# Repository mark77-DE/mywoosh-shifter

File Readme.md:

# MyWoosh Shifter

Kleine Bluetooth-Tastatur (BLE-HID) auf Basis eines ESP32-C3 Super Mini mit vier Tastern zum Schalten und Abbiegen in MyWoosh. Die Tastenbelegung lässt sich per Handy über eine kleine Konfigurationsseite ändern.

| Taster | Pin   | Standardtaste | Funktion         |
|--------|-------|---------------|------------------|
| 1      | GPIO4 | `i`           | hochschalten     |
| 2      | GPIO5 | `k`           | herunterschalten |
| 3      | GPIO6 | Pfeil links   | links abbiegen   |
| 4      | GPIO10 | Pfeil rechts | rechts abbiegen  |

## Hardware

- ESP32-C3 Super Mini (Bluetooth 5 LE)
- 4 Taster
- 1 LED mit Vorwiderstand (ca. 1 kΩ)

## Verdrahtung

Jeder Taster wird zwischen seinen GPIO-Pin und GND geschaltet. Externe Widerstände sind nicht nötig, der interne Pull-up wird verwendet.

```
GPIO4 ──[Taster 1]── GND
GPIO5 ──[Taster 2]── GND
GPIO6 ──[Taster 3]── GND
GPIO10 ──[Taster 4]── GND
```

## Build & Upload

Voraussetzung: [PlatformIO](https://platformio.org/) (VS Code Extension oder CLI).

```bash
pio run -t upload     # build and flash
pio device monitor    # serial output (115200 baud)
```

Falls der Upload nicht startet: BOOT gedrückt halten, dabei Reset drücken und erneut flashen.

## Koppeln

1. Auf dem Gerät mit MyWoosh (PC, Tablet, Handy, Apple TV) die Bluetooth-Einstellungen öffnen.
2. Nach **"MyWoosh Shifter"** suchen und koppeln.
3. In MyWoosh schalten die Taster nun hoch, runter und biegen links bzw. rechts ab (Standardbelegung).

## Status-LED

Eine LED an GPIO9 zeigt den Zustand an:

| LED                     | Bedeutung                              |
|-------------------------|----------------------------------------|
| blinkt langsam          | nicht verbunden, wartet auf Kopplung   |
| 3 Sekunden an, dann aus | mit dem Gerät verbunden                |
| blinkt schnell          | Konfigurationsmodus, Hotspot aktiv     |
| Doppelblinken           | Konfigurationsmodus, Client verbunden  |

Verdrahtung: 3V3, Vorwiderstand, LED, GPIO9. Die LED leuchtet also, wenn der Pin LOW ist.

Wichtig: GPIO9 ist ein Strapping-Pin (BOOT-Taster). Eine LED, die nach GND führt, würde den Pin beim Start nach unten ziehen und den ESP in den Download-Modus zwingen.

## Tasten per Handy zuordnen

Funktioniert auf Android und iOS, ohne App.

1. Taster 1 gedrückt halten und gleichzeitig den ESP mit Strom versorgen (z. B. USB einstecken). Nach etwa 1,5 Sekunden startet der Hotspot, die LED blinkt schnell.
2. Mit dem Handy das offene WLAN **MyWoosh-Shifter-Setup** verbinden (kein Passwort).
3. Die Konfigurationsseite öffnet sich meist automatisch. Sonst im Browser `http://192.168.4.1` aufrufen.
4. Für jeden Taster die gewünschte Taste wählen und auf **Speichern & neu starten** tippen.
5. Der ESP startet neu, der Hotspot ist danach wieder aus und die Belegung bleibt gespeichert.

Zur Auswahl stehen Buchstaben, Ziffern, F1 bis F12, Pfeiltasten, Enter, Esc, Leertaste, Tab, Bild auf/ab, Pos1 und Ende. Mit "keine" wird ein Taster deaktiviert.

Im Konfigurationsmodus ist Bluetooth aus, im normalen Betrieb ist WLAN aus. Die bestehende Kopplung mit MyWoosh bleibt davon unberührt.

## Konfiguration im Code

Oben in `src/main.cpp` lassen sich anpassen:

- `PIN_BTN`: GPIO-Pins der vier Taster
- `PIN_LED`, `LED_ACTIVE_LOW`: LED-Pin und Polarität (`true`: LED leuchtet bei LOW)
- `BLINK_MS`, `CONFIG_BLINK_MS`, `CONNECTED_SHOW_MS`: Blinkgeschwindigkeit und Leuchtdauer nach dem Verbinden
- `AP_SSID`: Name des Konfigurations-WLANs
- `CONFIG_HOLD_MS`: wie lange Taster 1 beim Einschalten gehalten werden muss
- `DEFAULT_KEYS`: Standardbelegung, solange noch nichts gespeichert wurde

In der Liste `buttons` legt das Feld `hold` fest, ob eine Taste nur kurz angetippt wird (`false`, Standard) oder gedrückt bleibt, solange der Taster gehalten wird (`true`).

## Hinweise

- Wichtig: Platform und Bibliothek müssen zusammenpassen. In der `platformio.ini` sind `espressif32@6.9.0` und `NimBLE-Arduino@1.4.3` fest gepinnt. Mit der neueren Platform (Arduino-Core 3.x) gibt es viele Build-Warnungen und einen Boot-Loop beim Start von BLE.
- Nach einem Wechsel der Versionen den Ordner `.pio` löschen und neu bauen.
- Android meldet beim Konfigurations-WLAN "Kein Internet". Verbunden bleiben, sonst springt das Handy ins Mobilfunknetz zurück.
- Falls beim Bauen ein Fehler wegen zu großem Programm kommt, in der `platformio.ini` die Zeile `board_build.partitions = huge_app.csv` ergänzen.
- Bei Kopplungsproblemen unter Windows den alten Bluetooth-Eintrag entfernen und neu koppeln.

## Projektstruktur

```
mywoosh-shifter/
├── platformio.ini
├── README.md
└── src/
    └── main.cpp
```

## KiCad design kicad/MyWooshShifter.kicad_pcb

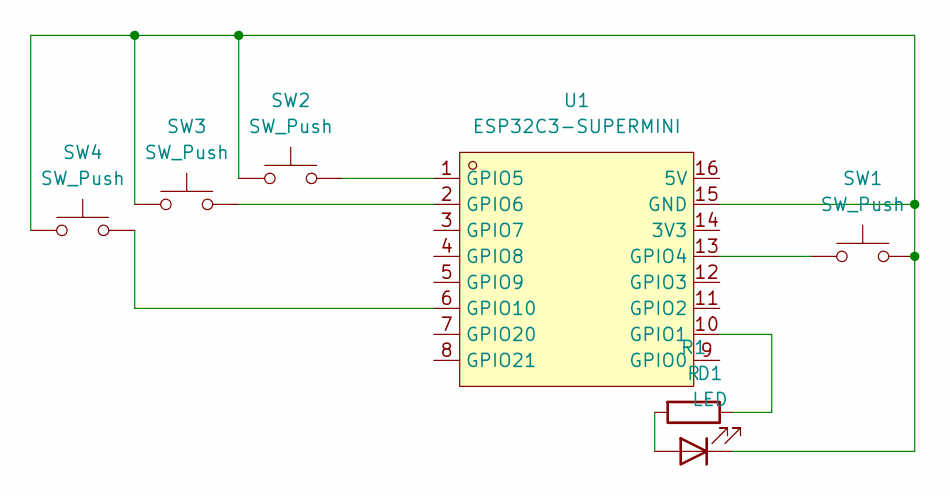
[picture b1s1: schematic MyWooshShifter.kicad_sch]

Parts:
D1: LED; LED_0805_2012Metric_Pad1.15x1.40mm_HandSolder
R1: R; R_0805_2012Metric_Pad1.20x1.40mm_HandSolder
SW1, SW2, SW3, SW4: SW_Push; SW_SPST_PTS645Sx43SMTR92
U1: ESP32C3-SUPERMINI; COMM-SMD_16P-L22.5-W18.0-P2.54-TL; MPN ESP32C3-SuperMini; LCSC Part C9900147397

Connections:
unnamed: D1.2 (A), R1.2
unnamed: D1.1 (K), SW1.2, SW2.1, SW3.1, SW4.1, U1.15 (GND)
unnamed: R1.1, U1.10 (GPIO1)
unnamed: SW1.1, U1.13 (GPIO4)
unnamed: SW2.2, U1.1 (GPIO5)
unnamed: SW3.2, U1.2 (GPIO6)
unnamed: SW4.2, U1.6 (GPIO10)

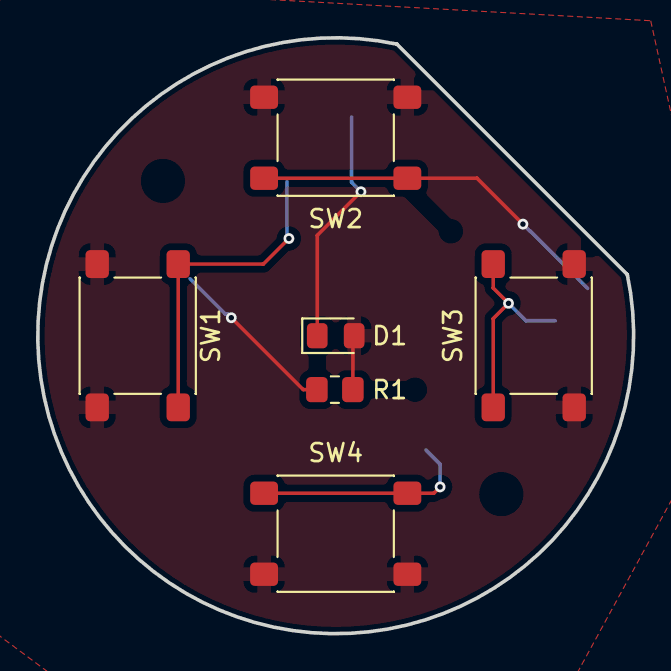
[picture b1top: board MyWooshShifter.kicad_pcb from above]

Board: 2 copper layers, 33.1 x 33.1 mm, 7 parts (1 on the bottom side), 7 nets.
